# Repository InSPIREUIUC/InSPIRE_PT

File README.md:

# InSPIRE
The official repo for InSPIRE

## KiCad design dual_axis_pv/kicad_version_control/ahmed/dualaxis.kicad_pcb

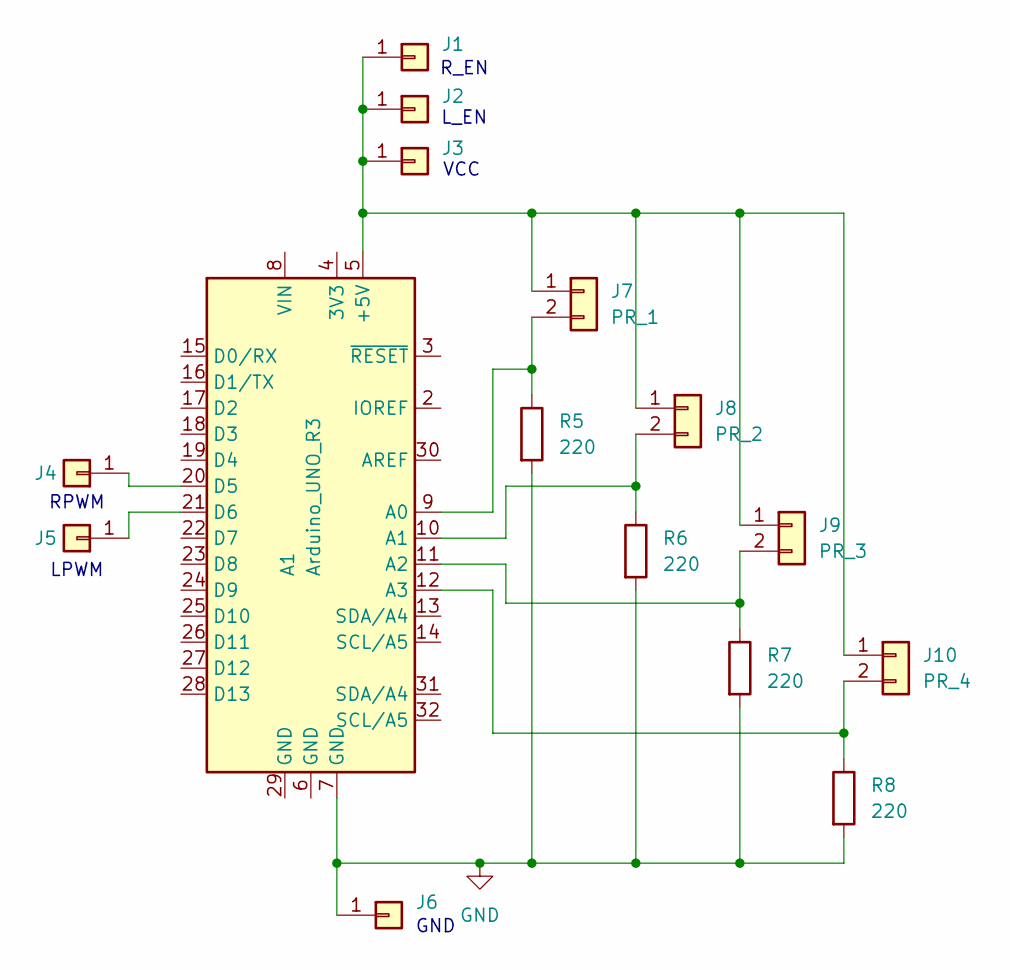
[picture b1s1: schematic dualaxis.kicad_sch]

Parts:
A1: Arduino_UNO_R3; Arduino_UNO_R3_WithMountingHoles
J1, J2, J3, J4, J5, J6: Conn_01x01; PinHeader_1x01_P2.54mm_Horizontal
J7: PR_1; PinHeader_1x02_P2.54mm_Horizontal
J8: PR_2; PinHeader_1x02_P2.54mm_Horizontal
J9: PR_3; PinHeader_1x02_P2.54mm_Horizontal
J10: PR_4; PinHeader_1x02_P2.54mm_Horizontal
R5, R6, R7, R8: 220; R_0805_2012Metric

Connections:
GND: A1.7 (GND), J6.1, R5.2, R6.2, R7.2, R8.2
unnamed: A1.5 (+5V), J1.1, J2.1, J3.1, J7.1, J8.1, J9.1, J10.1
unnamed: A1.9 (A0), J7.2, R5.1
unnamed: A1.10 (A1), J8.2, R6.1
unnamed: A1.11 (A2), J9.2, R7.1
unnamed: A1.12 (A3), J10.2, R8.1
unnamed: A1.20 (D5), J4.1
unnamed: A1.21 (D6), J5.1

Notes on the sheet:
LPWM
R_EN
VCC
GND
RPWM
L_EN

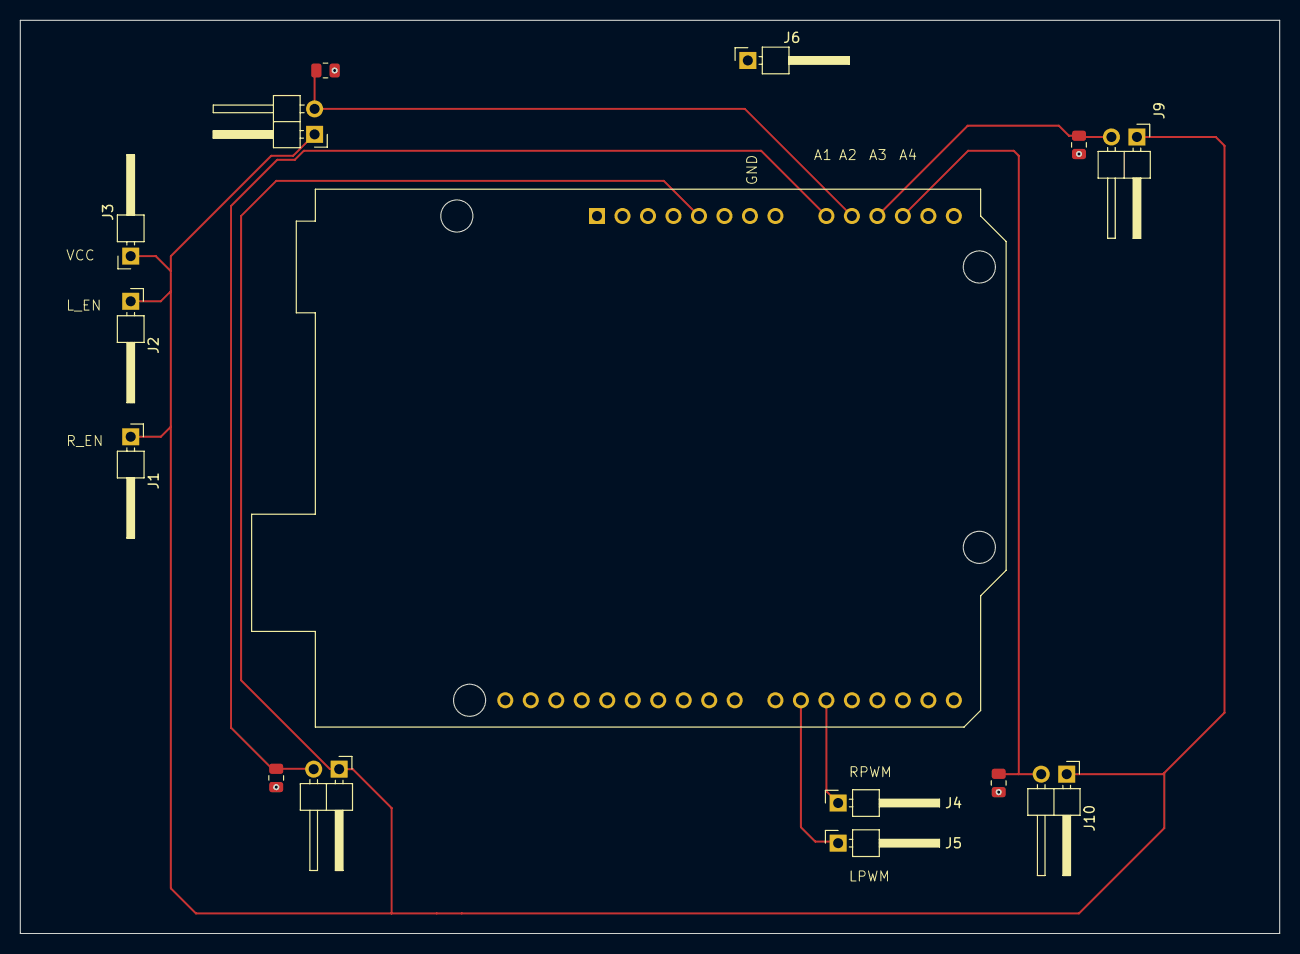
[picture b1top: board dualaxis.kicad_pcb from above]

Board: 2 copper layers, 125.5 x 91.0 mm, 15 parts (0 on the bottom side), 8 nets.

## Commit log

2023-11-04 added folders kb
2023-11-04 Create .gitignore
    added git ignore
2023-11-04 uploaded cascadeclassifier & dronevenv
2023-11-05 counter added, upper body detection, file renames
2023-11-17 roboflow
2024-02-02 rmvd api
2024-02-06 YOLOv8 MODEL
2024-02-09 worked on parse_arguments. tried to optimize performance and frame rate
2024-02-19 nano model
2024-03-01 Updated YoloV8 Model
2024-09-04 setup/cleanup
2024-09-05 tim onboard
2024-09-05 test
2024-09-06 joey joins github
2024-09-13 added joey.txt
2024-09-13 joy stick
2024-09-20 Added doc for calculating sun's position
2024-09-20 working copy of calculating sun's pos
2024-09-20 joy stick v2
2024-09-20 working code from Jaice and Rudy calculating sun's position
2024-09-20 working copy of calculating
2024-09-20 adding sketch_sep12a for sensing code
2024-09-27 added files
2024-10-04 z axis
2024-10-18 Telemetry started. Webcam feed works on local system but NOT local network
2024-10-25 worked on joystick
2024-11-22 adding test file
2024-11-22 version control kicad adi 11/21/2024
2024-11-22 deleted files
2024-11-22 added pcb and schematic 11/21
2024-12-06 project file
2024-12-06 trying to parse processed video to web server
2025-01-30 object orientation
2025-01-31 path change
2025-02-07 object fixes
2025-02-28 made
2025-03-07 telemetry prototype 1
2025-03-07 cleaning folders
2025-03-07 Added the joystick motor code
2025-03-14 cleanup ;
2025-04-03 interface
